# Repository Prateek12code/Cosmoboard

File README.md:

# Cosmoboard

**Cosmoboard** is a custom 75% mechanical keyboard with an open-top floating-switch design, custom PCB, MX hot-swap support, RGB lighting, and a 3D printed case and plate.

It is designed as a clean V1 keyboard build: simple enough to manufacture, but still custom enough to learn PCB design, keyboard matrices, routing, stabilizer placement, case design, and real hardware assembly.

> Type your ideas into orbit, one key at a time.

---

## Gallery

| PCB | Plate | 3D View |
|---|---|---|
|  |  |  |

---

## Why I Made This

I wanted to design and build my own keyboard from scratch instead of only using prebuilt keyboards.

Cosmoboard started as a learning project, but it slowly became a full custom keyboard design. Through this project, I worked on the keyboard layout, PCB routing, diode matrix, hot-swap sockets, stabilizer placement, case design, plate design, BOM planning, and manufacturing decisions.

The first plan used an FR4 plate, but I later changed it to a **3D printed plate** to reduce the total cost and make the project easier to prototype.

The goal of V1 is simple: make a keyboard that works, looks clean, and teaches me enough to build a better version later.

---

## Features

- Custom 75% keyboard layout
- MX-style mechanical switches
- MX hot-swap sockets
- 1N4148W SOD-123 diodes
- PCB-mount stabilizers
- WS2812B 5050 RGB LEDs
- Custom black PCB
- 3D printed switch plate
- 3D printed case
- Open-top floating-switch style
- Split case design for easier 3D printing
- Designed for real manufacturing and assembly

---

## Hardware Overview

| Part | Selected Item |
|---|---|
| PCB | Custom Cosmoboard PCB from JLCPCB |
| Switches | HMX Macchiato Linear Switches |
| Sockets | Kailh MX Hot-swap Sockets |
| Diodes | 1N4148W SOD-123 Diodes |
| Keycaps | Cherry Colour PBT Keycap Set |
| Stabilizers | Glorious GOAT PCB-mount Stabilizers |
| RGB | Worldsemi WS2812B 5050 LEDs |
| Plate | 3D Printed Plate |
| Case | 3D Printed Split Case |
| Filament | Numakers PLA+ Clear Transparent |

---

## PCB Details

| Item | Value |
|---|---|
| PCB Name | Cosmoboard-PCB_Y12 |
| PCB Width | Around 361.6 mm |
| PCB Thickness | 1.6 mm |
| PCB Color | Black |
| Switch Type | MX-style |
| Socket Type | Kailh MX Hot-swap |
| Diode Package | SOD-123 |
| Plate Type | 3D Printed |
| Case Type | Split 3D Printed Case |

---

## Case And Plate

The keyboard is wider than a normal Bambu Lab A1 build plate, so the case and plate are designed to be split into printable parts.

The case plan includes:

- Split 3D printed frame
- 3D printed switch plate
- Internal support ribs to reduce flex
- PCB screw mounting
- USB cutout
- Open-top floating-switch look

The FR4 plate was removed from the plan to reduce cost. The keyboard now uses a 3D printed plate and case.

---

## Bill Of Materials

The updated BOM is stored in:

```text
production/BOM.csv

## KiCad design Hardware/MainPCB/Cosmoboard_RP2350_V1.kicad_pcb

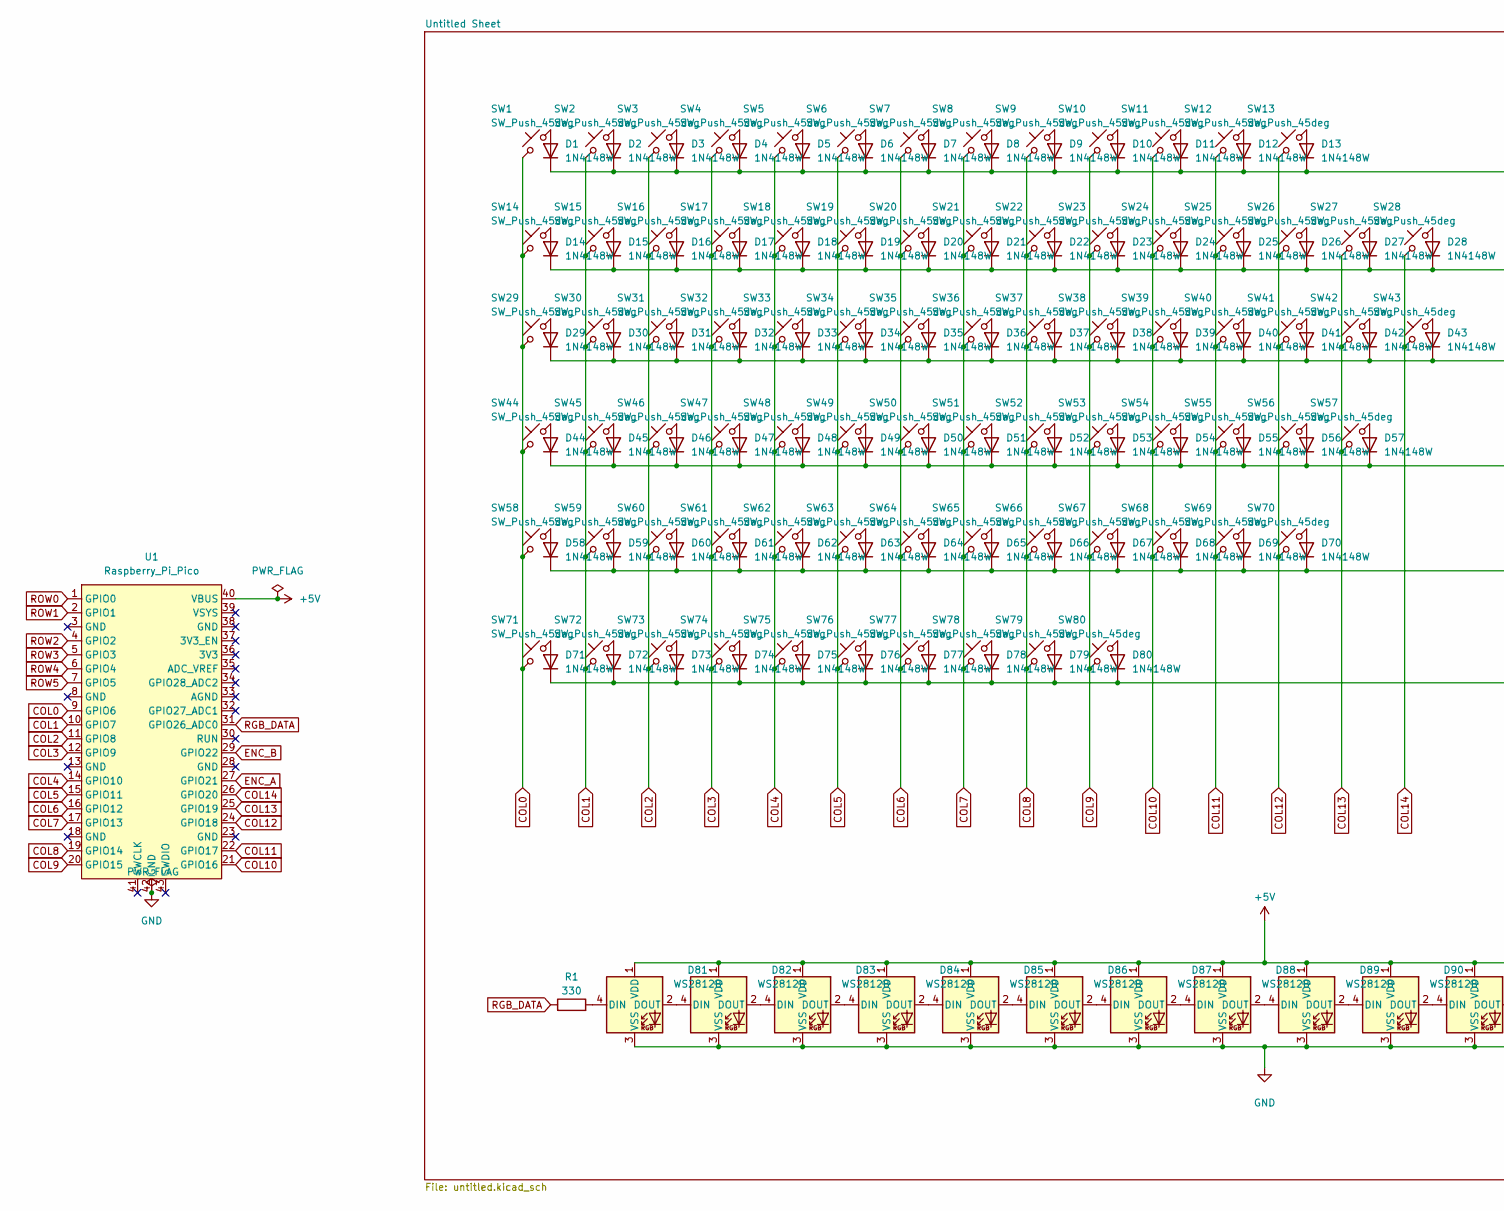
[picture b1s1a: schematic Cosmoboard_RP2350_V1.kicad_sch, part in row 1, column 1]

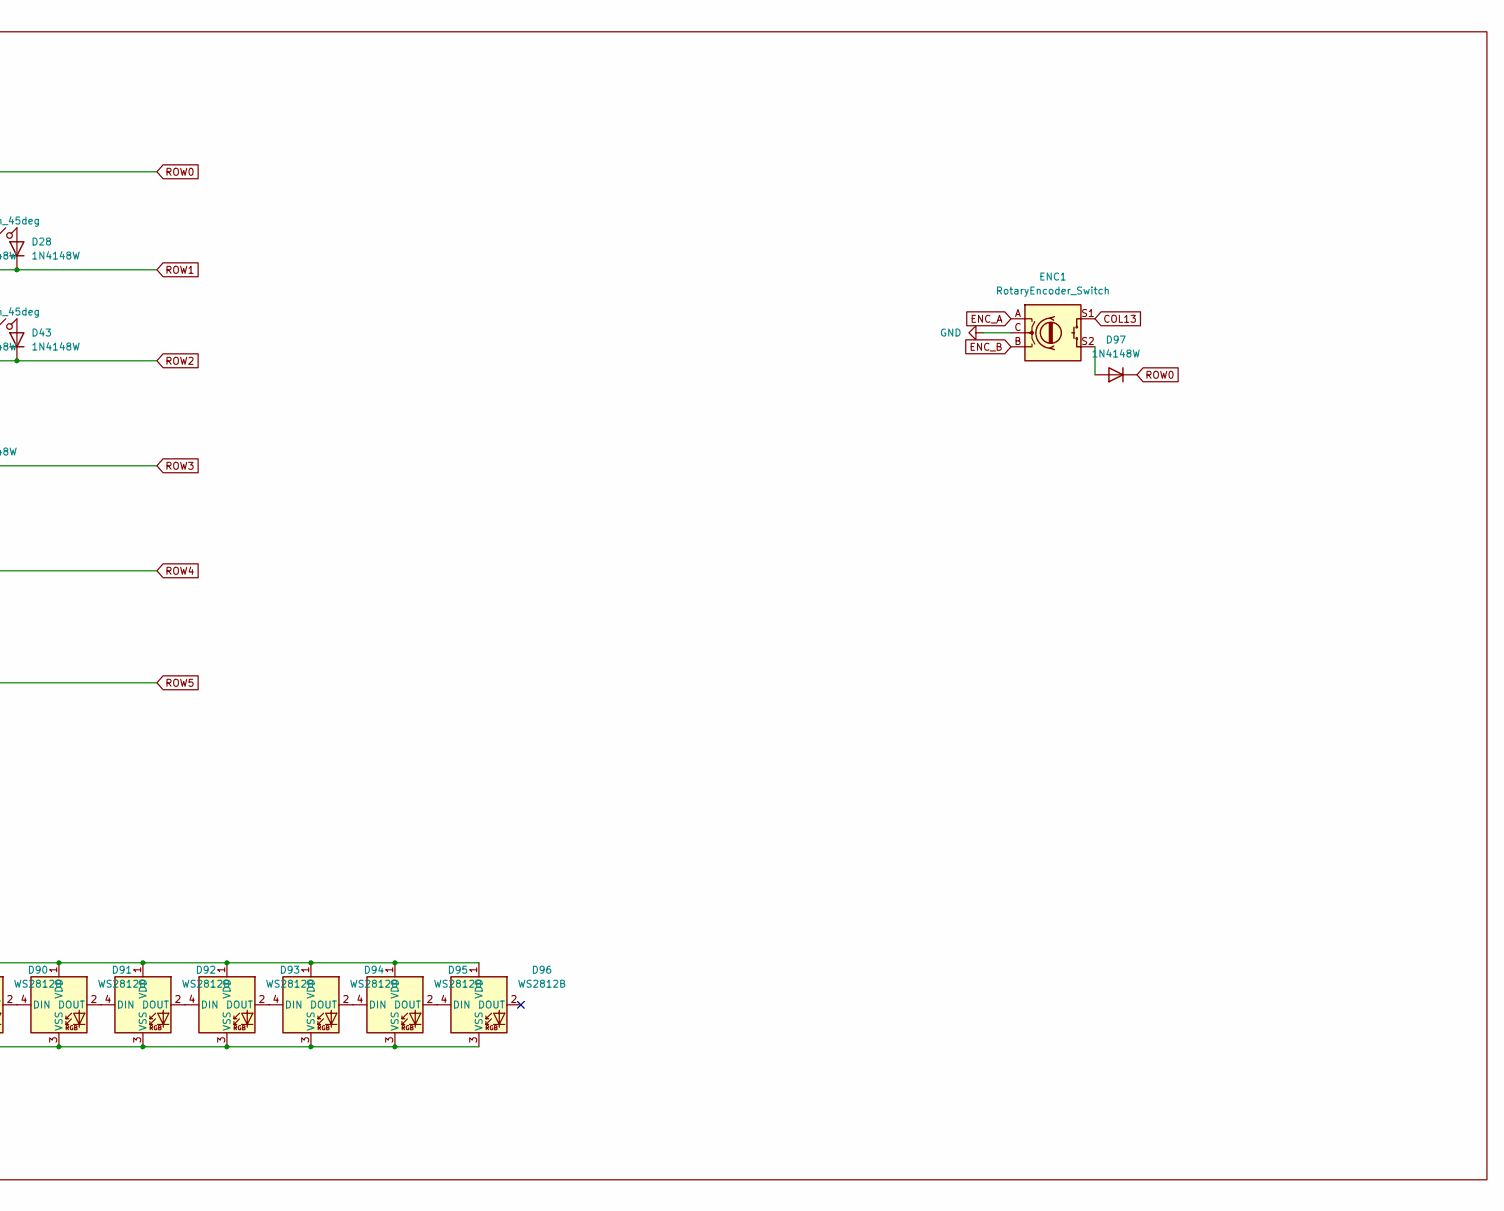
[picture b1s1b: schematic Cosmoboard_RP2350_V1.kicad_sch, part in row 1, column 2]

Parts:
D1, D2, D3, D4, D5, D6, D7, D8, D9, D10, D11, D12, D13, D14, D15, D16, D17, D18, D19, D20, D21, D22, D23, D24, D25, D26, D27, D28, D29, D30, D31, D32, D33, D34, D35, D36, D37, D38, D39, D40, D41, D42, D43, D44, D45, D46, D47, D48, D49, D50, D51, D52, D53, D54, D55, D56, D57, D58, D59, D60, D61, D62, D63, D64, D65, D66, D67, D68, D69, D70, D71, D72, D73, D74, D75, D76, D77, D78, D79, D80, D97: 1N4148W; D_SOD-123
D81, D82, D83, D84, D85, D86, D87, D88, D89, D90, D91, D92, D93, D94, D95, D96: WS2812B; LED_WS2812B_PLCC4_5.0x5.0mm_P3.2mm
ENC1: RotaryEncoder_Switch; Encoder_EC11_MX
R1: 330; R_0805_2012Metric
SW1, SW2, SW3, SW4, SW5, SW6, SW7, SW8, SW9, SW10, SW11, SW12, SW13, SW14, SW15, SW16, SW17, SW18, SW19, SW20, SW21, SW22, SW23, SW24, SW25, SW26, SW28, SW30, SW31, SW32, SW33, SW34, SW35, SW36, SW37, SW38, SW39, SW40, SW41, SW43, SW45, SW46, SW47, SW48, SW49, SW50, SW51, SW52, SW53, SW54, SW55, SW57, SW59, SW60, SW61, SW62, SW63, SW64, SW65, SW66, SW67, SW68, SW70, SW75, SW76, SW77, SW78, SW79, SW80: SW_Push_45deg; MX_Hotswap_1.00u
SW27: SW_Push_45deg; MX_Hotswap_2.00u
SW29, SW42: SW_Push_45deg; MX_Hotswap_1.50u
SW44, SW69: SW_Push_45deg; MX_Hotswap_1.75u
SW56, SW58: SW_Push_45deg; MX_Hotswap_2.25u
SW71, SW72, SW73: SW_Push_45deg; MX_Hotswap_1.25u
SW74: SW_Push_45deg; MX_Hotswap_6.25u
U1: Raspberry_Pi_Pico

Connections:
+5V: D81.1 (VDD), D82.1 (VDD), D83.1 (VDD), D84.1 (VDD), D85.1 (VDD), D86.1 (VDD), D87.1 (VDD), D88.1 (VDD), D89.1 (VDD), D90.1 (VDD), D91.1 (VDD), D92.1 (VDD), D93.1 (VDD), D94.1 (VDD), D95.1 (VDD), D96.1 (VDD), U1.40 (VBUS)
COL0: SW1.1, SW14.1, SW29.1, SW44.1, SW58.1, SW71.1, U1.9 (GPIO6)
COL1: SW2.1, SW15.1, SW30.1, SW45.1, SW59.1, SW72.1, U1.10 (GPIO7)
COL2: SW3.1, SW16.1, SW31.1, SW46.1, SW60.1, SW73.1, U1.11 (GPIO8)
COL3: SW4.1, SW17.1, SW32.1, SW47.1, SW61.1, SW74.1, U1.12 (GPIO9)
COL4: SW5.1, SW18.1, SW33.1, SW48.1, SW62.1, SW75.1, U1.14 (GPIO10)
COL5: SW6.1, SW19.1, SW34.1, SW49.1, SW63.1, SW76.1, U1.15 (GPIO11)
COL6: SW7.1, SW20.1, SW35.1, SW50.1, SW64.1, SW77.1, U1.16 (GPIO12)
COL7: SW8.1, SW21.1, SW36.1, SW51.1, SW65.1, SW78.1, U1.17 (GPIO13)
COL8: SW9.1, SW22.1, SW37.1, SW52.1, SW66.1, SW79.1, U1.19 (GPIO14)
COL9: SW10.1, SW23.1, SW38.1, SW53.1, SW67.1, SW80.1, U1.20 (GPIO15)
COL10: SW11.1, SW24.1, SW39.1, SW54.1, SW68.1, U1.21 (GPIO16)
COL11: SW12.1, SW25.1, SW40.1, SW55.1, SW69.1, U1.22 (GPIO17)
COL12: SW13.1, SW26.1, SW41.1, SW56.1, SW70.1, U1.24 (GPIO18)
COL13: ENC1.S1, SW27.1, SW42.1, SW57.1, U1.25 (GPIO19)
COL14: SW28.1, SW43.1, U1.26 (GPIO20)
ENC_A: ENC1.A, U1.27 (GPIO21)
ENC_B: ENC1.B, U1.29 (GPIO22)
GND: D81.3 (VSS), D82.3 (VSS), D83.3 (VSS), D84.3 (VSS), D85.3 (VSS), D86.3 (VSS), D87.3 (VSS), D88.3 (VSS), D89.3 (VSS), D90.3 (VSS), D91.3 (VSS), D92.3 (VSS), D93.3 (VSS), D94.3 (VSS), D95.3 (VSS), D96.3 (VSS), ENC1.C, U1.42 (GND)
unnamed: D1.2 (A), SW1.2
unnamed: D2.2 (A), SW2.2
unnamed: D3.2 (A), SW3.2
unnamed: D4.2 (A), SW4.2
unnamed: D5.2 (A), SW5.2
unnamed: D6.2 (A), SW6.2
unnamed: D7.2 (A), SW7.2
unnamed: D8.2 (A), SW8.2
unnamed: D9.2 (A), SW9.2
unnamed: D10.2 (A), SW10.2
unnamed: D11.2 (A), SW11.2
unnamed: D12.2 (A), SW12.2
unnamed: D13.2 (A), SW13.2
unnamed: D14.2 (A), SW14.2
unnamed: D15.2 (A), SW15.2
unnamed: D16.2 (A), SW16.2
unnamed: D17.2 (A), SW17.2
unnamed: D18.2 (A), SW18.2
unnamed: D19.2 (A), SW19.2
unnamed: D20.2 (A), SW20.2
unnamed: D21.2 (A), SW21.2
unnamed: D22.2 (A), SW22.2
unnamed: D23.2 (A), SW23.2
unnamed: D24.2 (A), SW24.2
unnamed: D25.2 (A), SW25.2
unnamed: D26.2 (A), SW26.2
unnamed: D27.2 (A), SW27.2
unnamed: D28.2 (A), SW28.2
unnamed: D29.2 (A), SW29.2
unnamed: D30.2 (A), SW30.2
unnamed: D31.2 (A), SW31.2
unnamed: D32.2 (A), SW32.2
unnamed: D33.2 (A), SW33.2
unnamed: D34.2 (A), SW34.2
unnamed: D35.2 (A), SW35.2
unnamed: D36.2 (A), SW36.2
unnamed: D37.2 (A), SW37.2
unnamed: D38.2 (A), SW38.2
unnamed: D39.2 (A), SW39.2
unnamed: D40.2 (A), SW40.2
unnamed: D41.2 (A), SW41.2
unnamed: D42.2 (A), SW42.2
unnamed: D43.2 (A), SW43.2
unnamed: D44.2 (A), SW44.2
unnamed: D45.2 (A), SW45.2
unnamed: D46.2 (A), SW46.2
unnamed: D47.2 (A), SW47.2
unnamed: D48.2 (A), SW48.2
unnamed: D49.2 (A), SW49.2
unnamed: D50.2 (A), SW50.2
unnamed: D51.2 (A), SW51.2
unnamed: D52.2 (A), SW52.2
unnamed: D53.2 (A), SW53.2
unnamed: D54.2 (A), SW54.2
unnamed: D55.2 (A), SW55.2
unnamed: D56.2 (A), SW56.2
unnamed: D57.2 (A), SW57.2
unnamed: D58.2 (A), SW58.2
unnamed: D59.2 (A), SW59.2
unnamed: D60.2 (A), SW60.2
unnamed: D61.2 (A), SW61.2
unnamed: D62.2 (A), SW62.2
unnamed: D63.2 (A), SW63.2
unnamed: D64.2 (A), SW64.2
unnamed: D65.2 (A), SW65.2
unnamed: D66.2 (A), SW66.2
unnamed: D67.2 (A), SW67.2
unnamed: D68.2 (A), SW68.2
unnamed: D69.2 (A), SW69.2
unnamed: D70.2 (A), SW70.2
unnamed: D71.2 (A), SW71.2
unnamed: D72.2 (A), SW72.2
unnamed: D73.2 (A), SW73.2
unnamed: D74.2 (A), SW74.2
unnamed: D75.2 (A), SW75.2
unnamed: D76.2 (A), SW76.2
unnamed: D77.2 (A), SW77.2
unnamed: D78.2 (A), SW78.2
unnamed: D79.2 (A), SW79.2
unnamed: D80.2 (A), SW80.2
unnamed: D81.4 (DIN), R1.2
unnamed: D81.2 (DOUT), D82.4 (DIN)
unnamed: D82.2 (DOUT), D83.4 (DIN)
unnamed: D83.2 (DOUT), D84.4 (DIN)
unnamed: D84.2 (DOUT), D85.4 (DIN)
unnamed: D85.2 (DOUT), D86.4 (DIN)
unnamed: D86.2 (DOUT), D87.4 (DIN)
unnamed: D87.2 (DOUT), D88.4 (DIN)
unnamed: D88.2 (DOUT), D89.4 (DIN)
unnamed: D89.2 (DOUT), D90.4 (DIN)
unnamed: D90.2 (DOUT), D91.4 (DIN)
unnamed: D91.2 (DOUT), D92.4 (DIN)
unnamed: D92.2 (DOUT), D93.4 (DIN)
unnamed: D93.2 (DOUT), D94.4 (DIN)
unnamed: D94.2 (DOUT), D95.4 (DIN)
unnamed: D95.2 (DOUT), D96.4 (DIN)
unnamed: D97.2 (A), ENC1.S2
RGB_DATA: R1.1, U1.31 (GPIO26_ADC0)
ROW0: D1.1 (K), D2.1 (K), D3.1 (K), D4.1 (K), D5.1 (K), D6.1 (K), D7.1 (K), D8.1 (K), D9.1 (K), D10.1 (K), D11.1 (K), D12.1 (K), D13.1 (K), D97.1 (K), U1.1 (GPIO0)
ROW1: D14.1 (K), D15.1 (K), D16.1 (K), D17.1 (K), D18.1 (K), D19.1 (K), D20.1 (K), D21.1 (K), D22.1 (K), D23.1 (K), D24.1 (K), D25.1 (K), D26.1 (K), D27.1 (K), D28.1 (K), U1.2 (GPIO1)
ROW2: D29.1 (K), D30.1 (K), D31.1 (K), D32.1 (K), D33.1 (K), D34.1 (K), D35.1 (K), D36.1 (K), D37.1 (K), D38.1 (K), D39.1 (K), D40.1 (K), D41.1 (K), D42.1 (K), D43.1 (K), U1.4 (GPIO2)
ROW3: D44.1 (K), D45.1 (K), D46.1 (K), D47.1 (K), D48.1 (K), D49.1 (K), D50.1 (K), D51.1 (K), D52.1 (K), D53.1 (K), D54.1 (K), D55.1 (K), D56.1 (K), D57.1 (K), U1.5 (GPIO3)
ROW4: D58.1 (K), D59.1 (K), D60.1 (K), D61.1 (K), D62.1 (K), D63.1 (K), D64.1 (K), D65.1 (K), D66.1 (K), D67.1 (K), D68.1 (K), D69.1 (K), D70.1 (K), U1.6 (GPIO4)
ROW5: D71.1 (K), D72.1 (K), D73.1 (K), D74.1 (K), D75.1 (K), D76.1 (K), D77.1 (K), D78.1 (K), D79.1 (K), D80.1 (K), U1.7 (GPIO5)

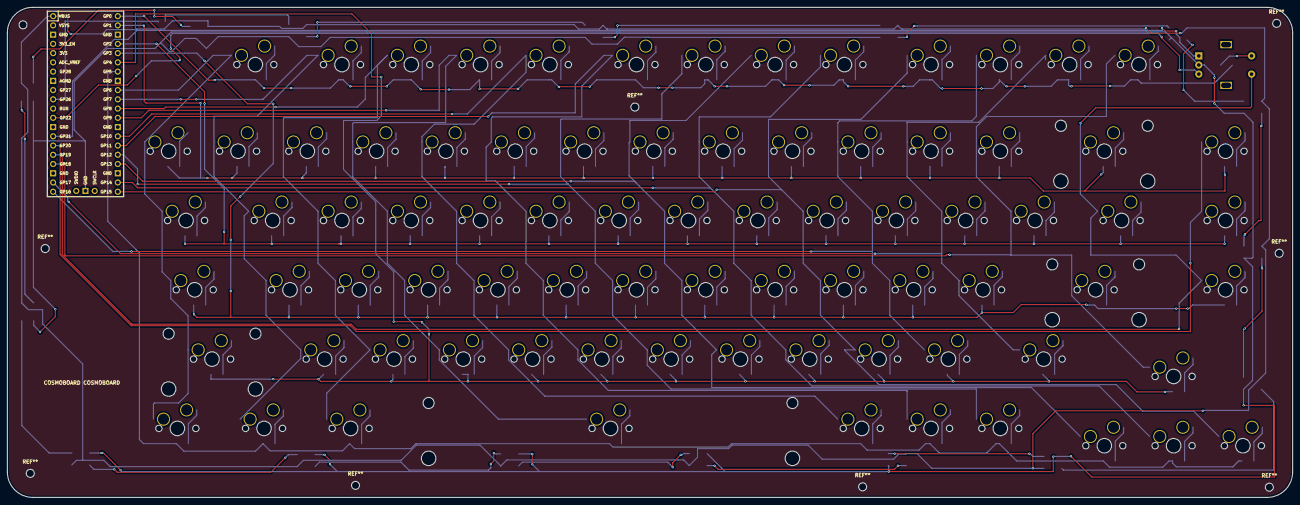
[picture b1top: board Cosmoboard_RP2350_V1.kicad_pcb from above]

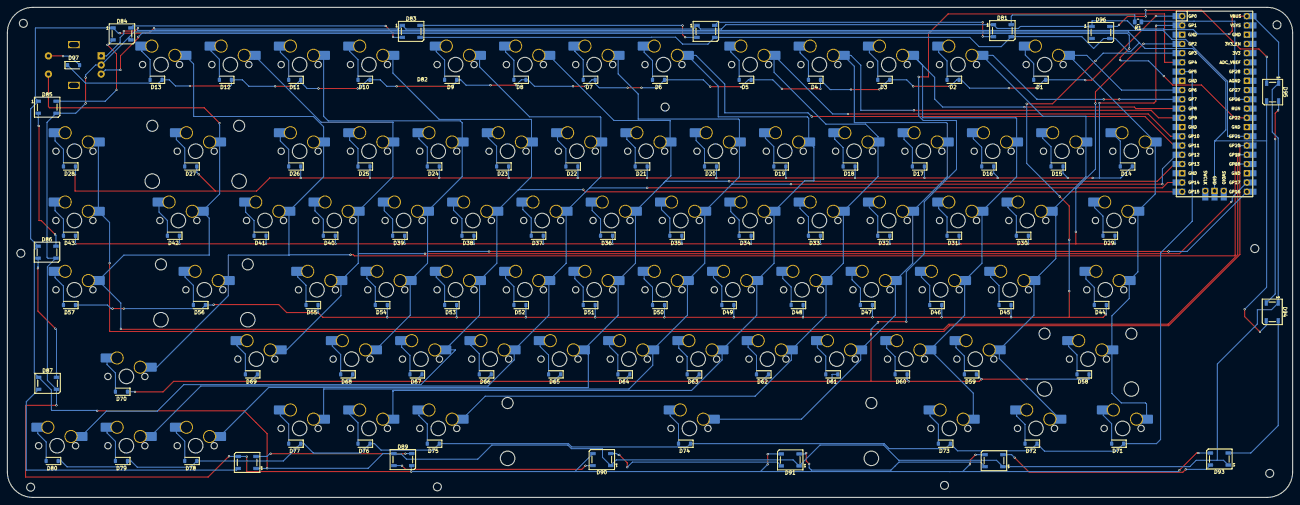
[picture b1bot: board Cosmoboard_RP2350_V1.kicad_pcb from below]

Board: 2 copper layers, 353.3 x 134.7 mm, 180 parts (179 on the bottom side), 123 nets.

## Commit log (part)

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2026-06-07 Update Gallery section in README
    Remove image paths from the Gallery section.
2026-06-07 Create images folder
2026-06-07 Rename Screenshot 2026-06-07 161714.png to PCB.png
2026-06-07 Rename Screenshot 2026-06-07 161739.png to Plate.png
2026-06-07 Rename Screenshot 2026-06-07 184820.png to 3D.png
2026-06-07 Add images to the Gallery section in README
2026-06-11 Add initial README for Firmware project
2026-06-11 Add initial README for Case / Bottom Tray
2026-06-11 Revise README for clarity and add gallery section
    Updated the README to improve clarity and organization, added a gallery section, and refined hardware details.
